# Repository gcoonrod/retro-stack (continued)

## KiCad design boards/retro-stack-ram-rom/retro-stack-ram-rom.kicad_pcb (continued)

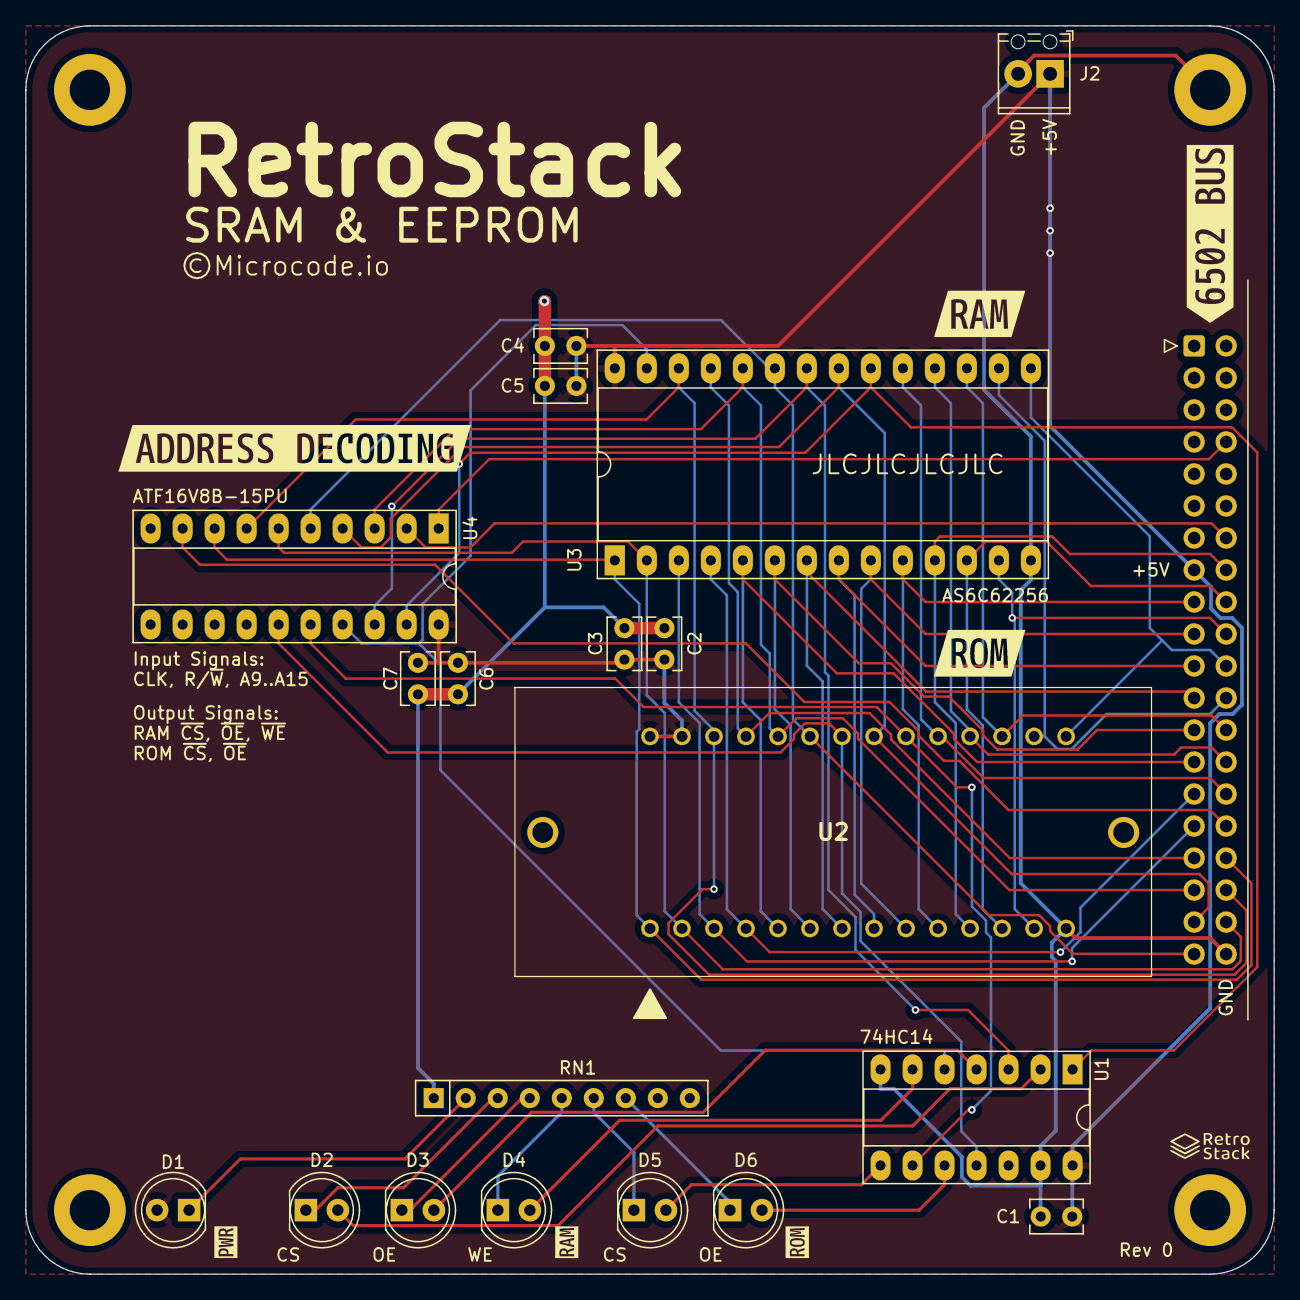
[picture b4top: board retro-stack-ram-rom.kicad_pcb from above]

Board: 2 copper layers, 99.1 x 99.1 mm, 31 parts (0 on the bottom side), 44 nets.

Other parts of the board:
kibuzzard-642C367F: G***; kibuzzard-642C367F
kibuzzard-642DBD4D: G***; kibuzzard-642DBD4D
kibuzzard-642DBD42: G***; kibuzzard-642DBD42
kibuzzard-642DC482: G***; kibuzzard-642DC482
kibuzzard-642888DE: G***; kibuzzard-642888DE
kibuzzard-6448402D: G***; kibuzzard-6448402D
kibuzzard-64484043: G***; kibuzzard-64484043

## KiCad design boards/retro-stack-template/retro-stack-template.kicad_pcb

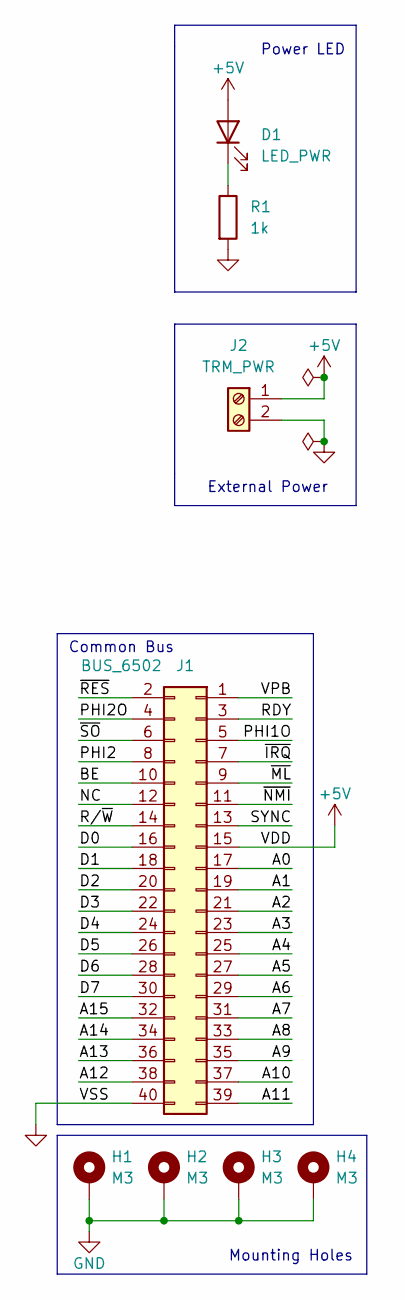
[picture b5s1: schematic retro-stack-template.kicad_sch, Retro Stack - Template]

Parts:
D1: LED_PWR; LED_D5.0mm
H1, H2, H3, H4: M3; MountingHole_3.2mm_M3_ISO7380_Pad
J1: BUS_6502; IDC-Header_2x20_P2.54mm_Horizontal
J2: TRM_PWR; TerminalBlock_Phoenix_MPT-0,5-2-2.54_1x02_P2.54mm_Horizontal; Mfr Part 1725656
R1: 1k; R_Axial_DIN0204_L3.6mm_D1.6mm_P5.08mm_Horizontal

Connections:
+5V: D1.2 (A), J1.15, J2.1
/A0: J1.17
/A1: J1.19
/A2: J1.21
/A3: J1.23
/A4: J1.25
/A5: J1.27
/A6: J1.29
/A7: J1.31
/A8: J1.33
/A9: J1.35
/A10: J1.37
/A11: J1.39
/A12: J1.38
/A13: J1.36
/A14: J1.34
/A15: J1.32
/BE: J1.10
/D0: J1.16
/D1: J1.18
/D2: J1.20
/D3: J1.22
/D4: J1.24
/D5: J1.26
/D6: J1.28
/D7: J1.30
/NC: J1.12
/PHI1O: J1.5
/PHI2: J1.8
/PHI2O: J1.4
/RDY: J1.3
/R/~W: J1.14
/SYNC: J1.13
/VPB: J1.1
/~IRQ: J1.7
/~ML: J1.9
/~NMI: J1.11
/~RES: J1.2
/~SO: J1.6
GND: H1.1, H2.1, H3.1, H4.1, J1.40, J2.2, R1.2
unnamed: D1.1 (K), R1.1

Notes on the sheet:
External Power
Common Bus
Power LED
Mounting Holes

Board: 2 copper layers, 11 parts (0 on the bottom side), 3 nets, no tracks yet.

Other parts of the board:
kibuzzard-642C36EF: G***; kibuzzard-642C36EF
kibuzzard-642C367F: G***; kibuzzard-642C367F
kibuzzard-642888DE: G***; kibuzzard-642888DE

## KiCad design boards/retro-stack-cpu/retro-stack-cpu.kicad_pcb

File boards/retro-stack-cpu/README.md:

# RetroStack - W65C02S CPU & High Speed Clock Module

This module contains the W65C02S CPU, a selectable high speed oscillator, and a selectable DS1813 reset signal manager.

## Schematic

Current schematic [pdf](./assets/schematic.pdf).

## PCB Layout & Render

## Known Issues

N/A

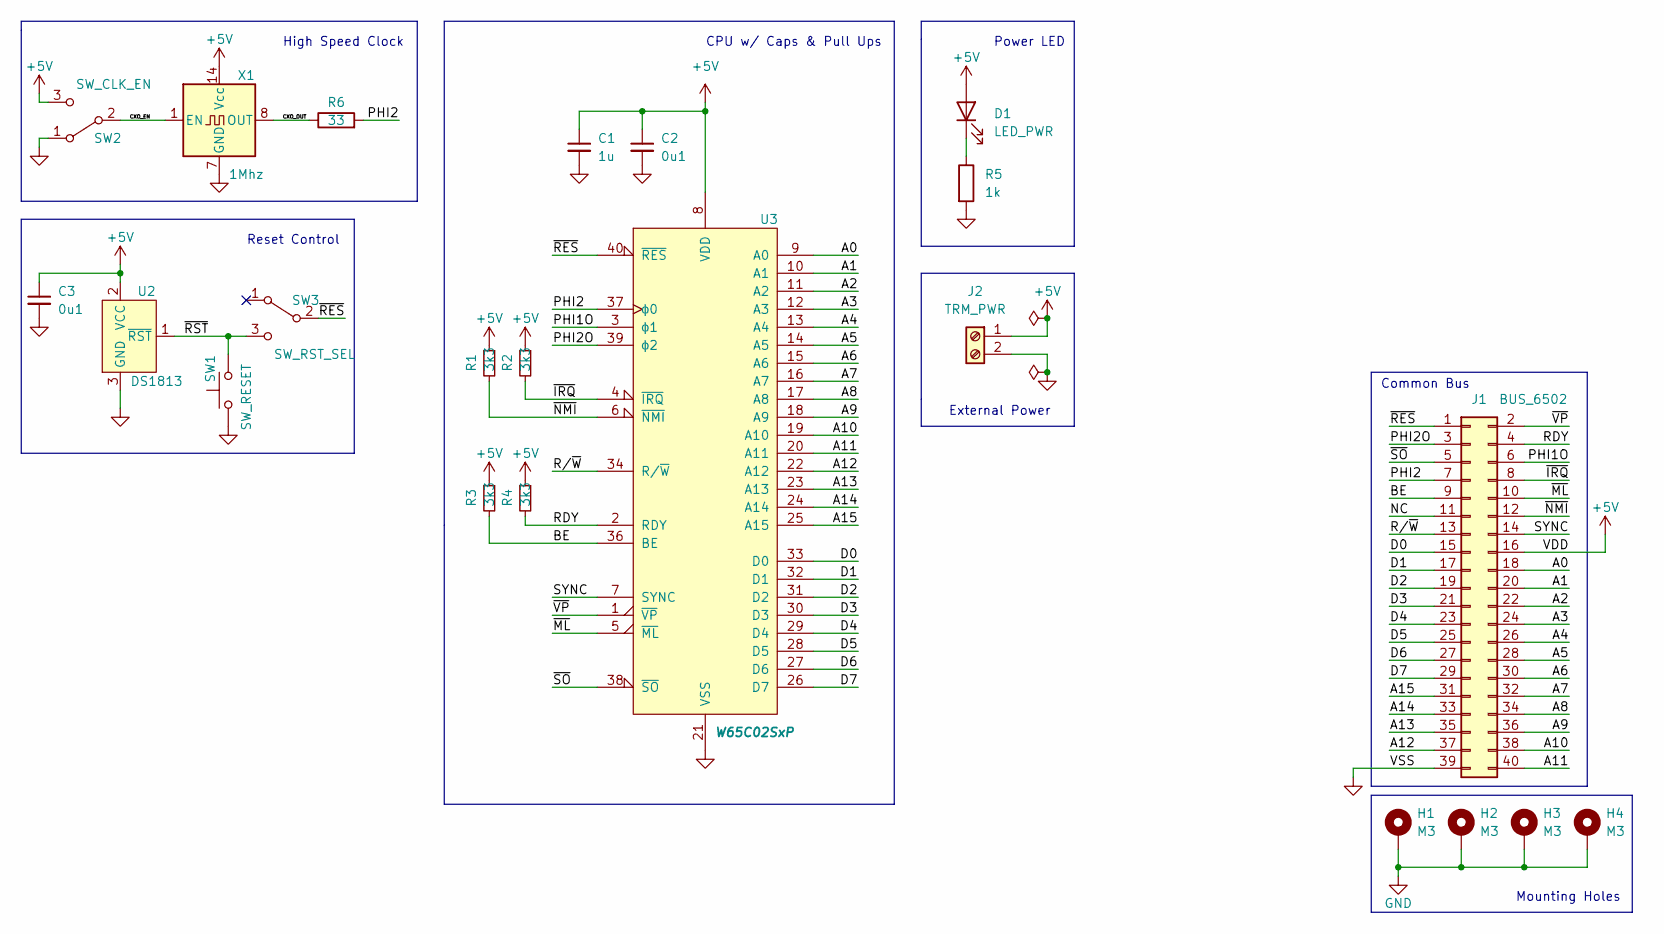
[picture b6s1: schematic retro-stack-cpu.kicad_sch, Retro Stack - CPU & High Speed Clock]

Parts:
C1: 1u; C_Rect_L4.0mm_W2.5mm_P2.50mm; Mfr Part FA18X7R1E105KRU06
C2, C3: 0u1; C_Rect_L4.0mm_W2.5mm_P2.50mm; Mfr Part RCER71E104K0A2H03B
D1: LED_PWR; LED_D5.0mm
H1, H2, H3, H4: M3; MountingHole_3.2mm_M3_ISO7380_Pad
J1: BUS_6502; PinSocket_2x20_P2.54mm_Vertical; Mfr Part 1979
J2: TRM_PWR; TerminalBlock_Phoenix_MPT-0,5-2-2.54_1x02_P2.54mm_Horizontal; Mfr Part 1725656
R1, R2, R3, R4: 3k3; R_Axial_DIN0204_L3.6mm_D1.6mm_P5.08mm_Horizontal; Mfr Part MBA02040C3301FRP00
R5: 1k; R_Axial_DIN0204_L3.6mm_D1.6mm_P5.08mm_Horizontal; Mfr Part MBA02040C1001FCT00
R6: 33; R_Axial_DIN0204_L3.6mm_D1.6mm_P5.08mm_Horizontal; Mfr Part MBA02040C3309FC100
SW1: SW_RESET; SW_Tactile_SPST_Angled_PTS645Vx58-2LFS; Mfr Part TS11-674-73-BK-100-RA-D
SW2: SW_CLK_EN; LC1258EENP1RLGR; Mfr Part LC1258EENP1RLGR
SW3: SW_RST_SEL; LC1258EENP1RLGR; Mfr Part LC1258EENP1RLGR
U2: DS1813; TO-92; Mfr Part DS1813-10+T&R
U3: W65C02SxP; DIP-40_W15.24mm_Socket_LongPads; Mfr Part W65C02S6TPG-14
X1: 1Mhz; Oscillator_DIP-14; Mfr Part MXO45T-2C-1M0000

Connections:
+5V: C1.1, C2.1, C3.1, D1.2 (A), J1.16, J2.1, R1.1, R2.1, R3.1, R4.1, SW2.3 (C), U2.2 (VCC), U3.8 (VDD), X1.14 (Vcc)
/A0: J1.18, U3.9 (A0)
/A1: J1.20, U3.10 (A1)
/A2: J1.22, U3.11 (A2)
/A3: J1.24, U3.12 (A3)
/A4: J1.26, U3.13 (A4)
/A5: J1.28, U3.14 (A5)
/A6: J1.30, U3.15 (A6)
/A7: J1.32, U3.16 (A7)
/A8: J1.34, U3.17 (A8)
/A9: J1.36, U3.18 (A9)
/A10: J1.38, U3.19 (A10)
/A11: J1.40, U3.20 (A11)
/A12: J1.37, U3.22 (A12)
/A13: J1.35, U3.23 (A13)
/A14: J1.33, U3.24 (A14)
/A15: J1.31, U3.25 (A15)
/BE: J1.9, R3.2, U3.36 (BE)
/CXO_EN: SW2.2 (B), X1.1 (EN)
/CXO_OUT: R6.1, X1.8 (OUT)
/D0: J1.15, U3.33 (D0)
/D1: J1.17, U3.32 (D1)
/D2: J1.19, U3.31 (D2)
/D3: J1.21, U3.30 (D3)
/D4: J1.23, U3.29 (D4)
/D5: J1.25, U3.28 (D5)
/D6: J1.27, U3.27 (D6)
/D7: J1.29, U3.26 (D7)
/NC: J1.11
/PHI1O: J1.6, U3.3 (ϕ1)
/PHI2: J1.7, R6.2, U3.37 (ϕ0)
/PHI2O: J1.3, U3.39 (ϕ2)
/RDY: J1.4, R4.2, U3.2 (RDY)
/R/~W: J1.13, U3.34 (R/~W)
/SYNC: J1.14, U3.7 (SYNC)
/~IRQ: J1.8, R2.2, U3.4 (~IRQ)
/~ML: J1.10, U3.5 (~ML)
/~NMI: J1.12, R1.2, U3.6 (~NMI)
/~RES: J1.1, SW3.2 (B), U3.40 (~RES)
/~RST: SW1.2, SW3.3 (C), U2.1 (~RST)
/~SO: J1.5, U3.38 (~SO)
/~VP: J1.2, U3.1 (~VP)
GND: C1.2, C2.2, C3.2, H1.1, H2.1, H3.1, H4.1, J1.39, J2.2, R5.2, SW1.1, SW2.1 (A), U2.3 (GND), U3.21 (VSS), X1.7 (GND)
unnamed: D1.1 (K), R5.1

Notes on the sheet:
CPU w/ Caps & Pull Ups
Common Bus
Power LED
High Speed Clock
External Power
Reset Control
Mounting Holes

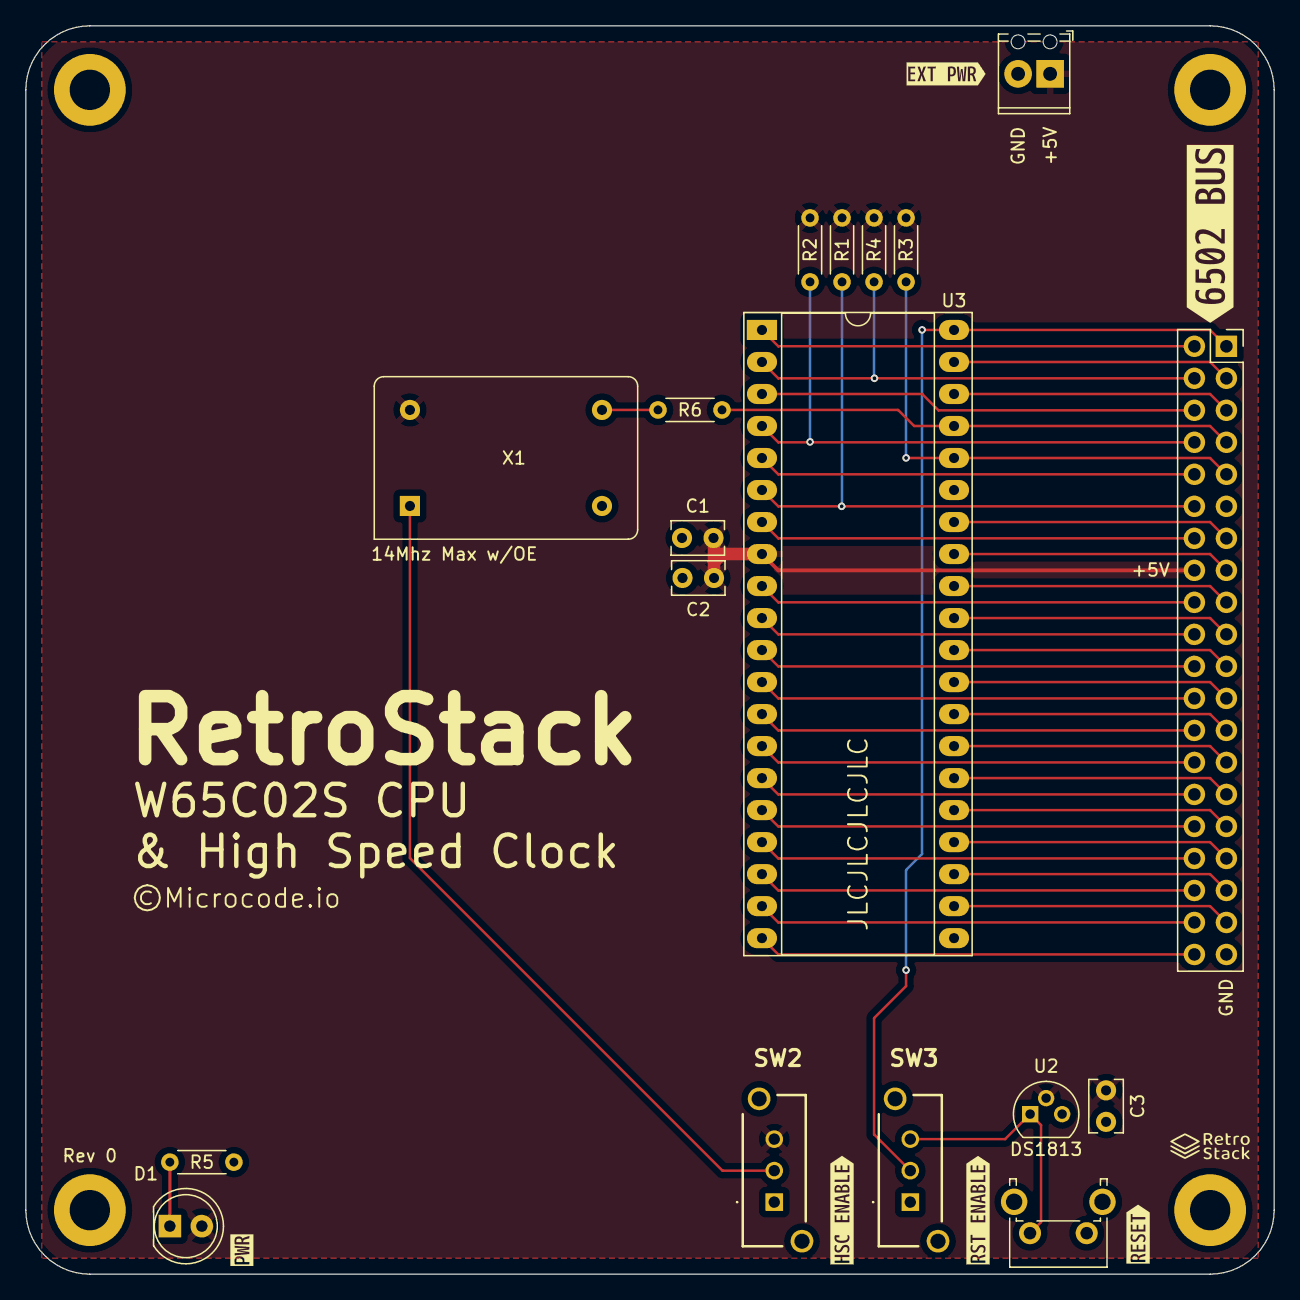
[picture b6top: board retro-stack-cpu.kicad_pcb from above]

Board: 2 copper layers, 99.1 x 99.1 mm, 28 parts (0 on the bottom side), 43 nets.

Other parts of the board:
kibuzzard-642C33B0: G***; kibuzzard-642C33B0
kibuzzard-642C36EF: G***; kibuzzard-642C36EF
kibuzzard-642C367F: G***; kibuzzard-642C367F
kibuzzard-642C3375: G***; kibuzzard-642C3375
kibuzzard-642C3403: G***; kibuzzard-642C3403
kibuzzard-642888DE: G***; kibuzzard-642888DE

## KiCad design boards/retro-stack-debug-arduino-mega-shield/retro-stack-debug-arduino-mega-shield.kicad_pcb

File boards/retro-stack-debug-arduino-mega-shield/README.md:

# RetroStack - Arduino Mega Debug Shield

This Arduino Mega shield is designed to easily connect to the RetroStack Debug board via a 40 pin IDC connector.

## Schematic

Current schematic [pdf](./assets/schematic.pdf).

## PCB Layout & Render

## Known Issues

- 6502 Bus is backwards. Pin 1 should be RESB but is VPB instead.
- PHI2 should be connected to one of the digital pins that support interrupts (2, 3, etc)
  - Consider adding jumpers to send a few signals to interrupt pins.
- Power seems to be leaking between the arduino and the RetroStack. Needs diodes?

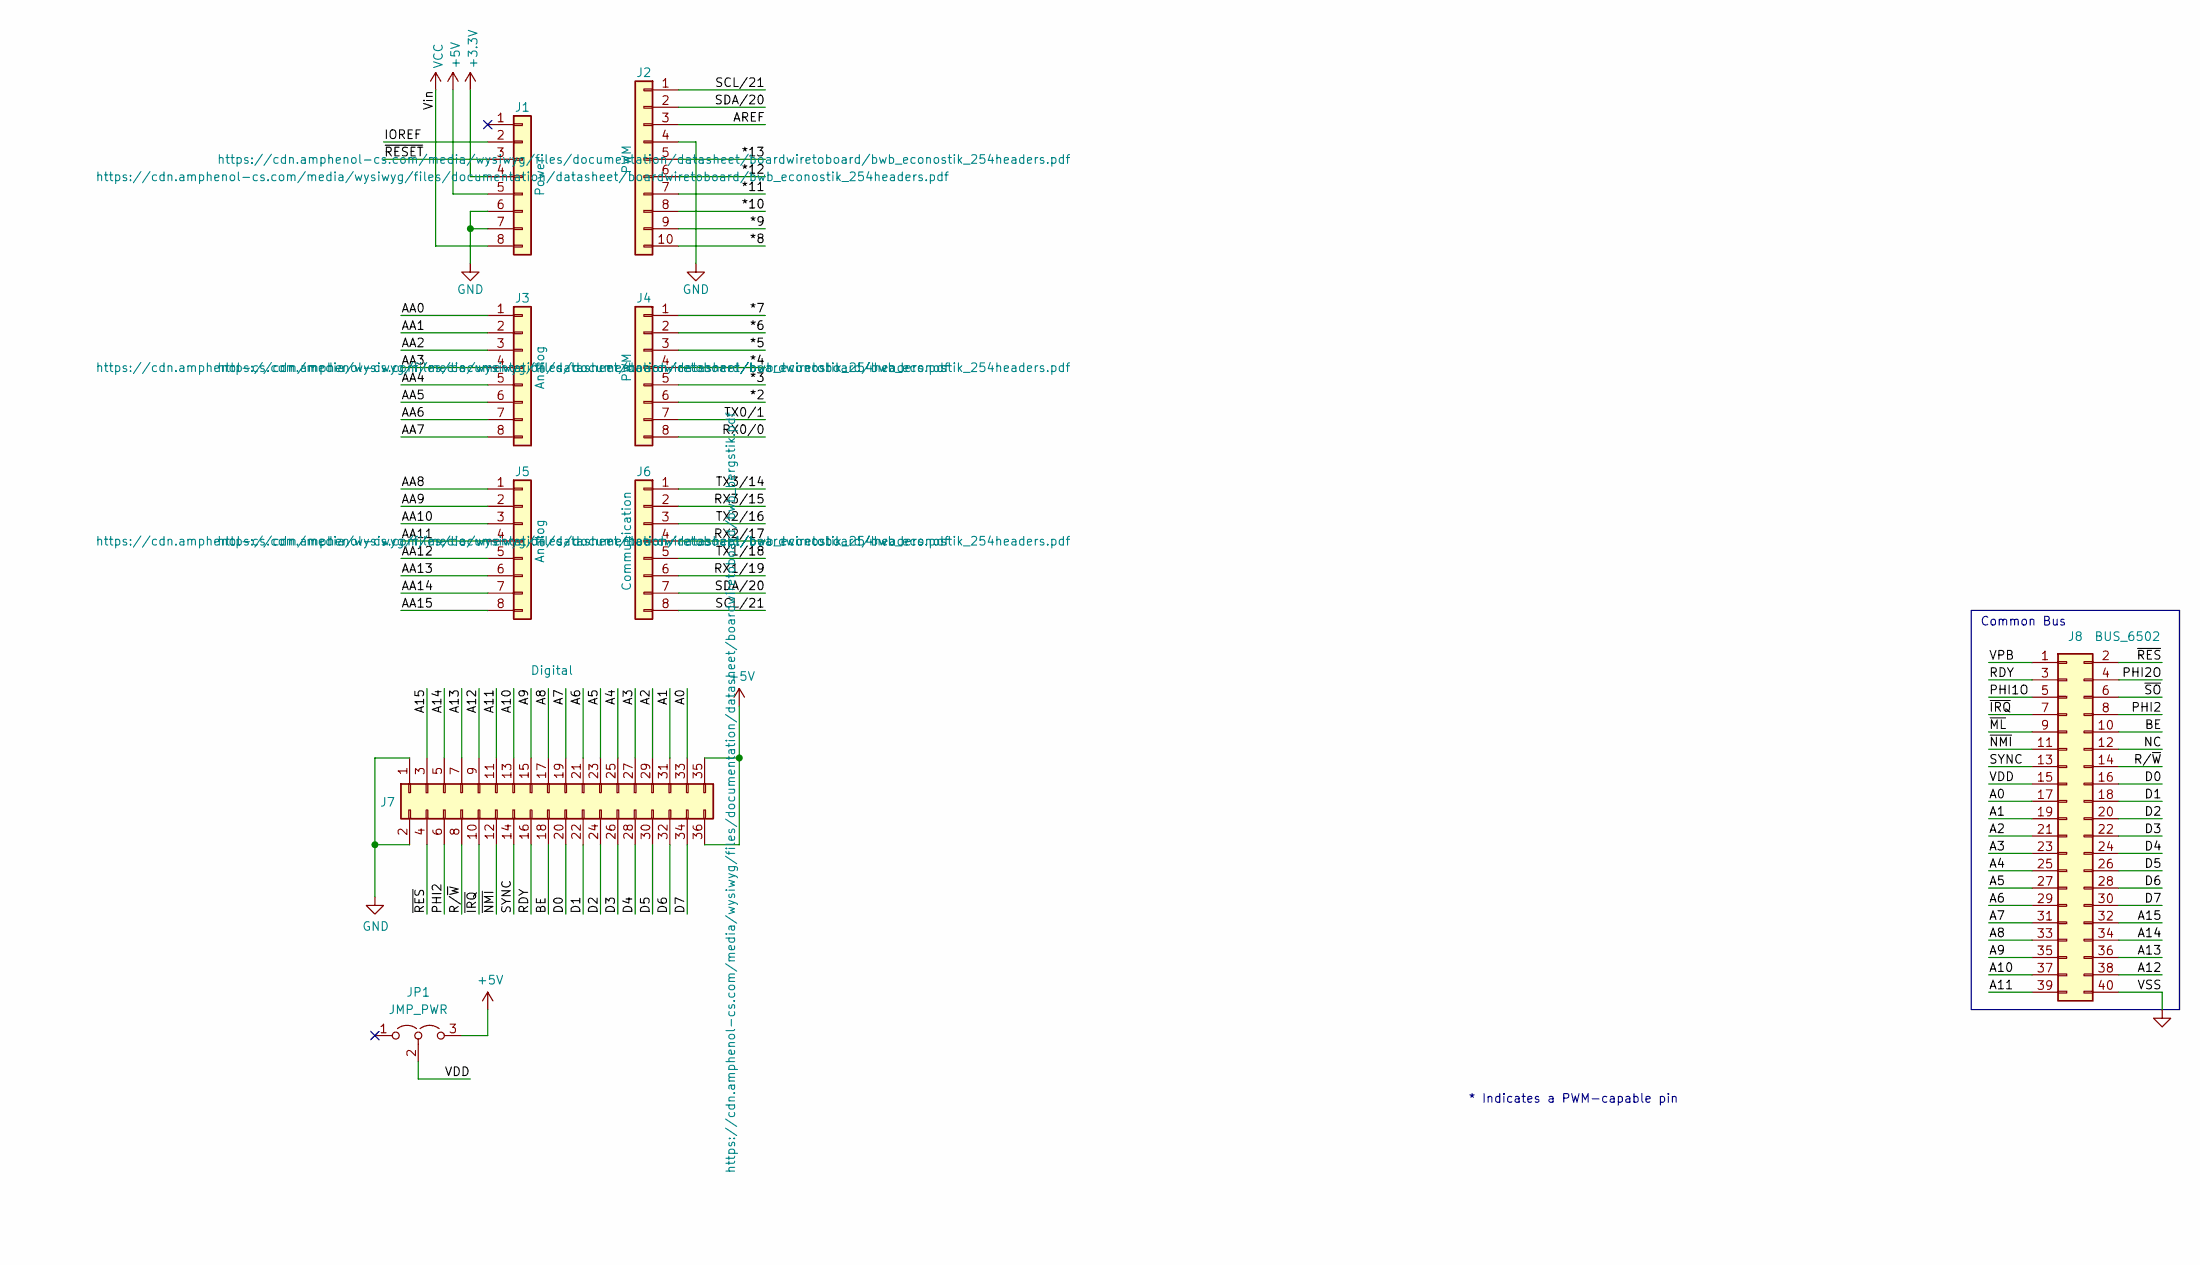
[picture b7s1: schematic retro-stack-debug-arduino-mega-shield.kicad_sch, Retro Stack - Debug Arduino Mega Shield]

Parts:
J1: Power; PinSocket_1x08_P2.54mm_Vertical; Mfr Part 10129378-908001BLF
J2: PWM; PinSocket_1x10_P2.54mm_Vertical; Mfr Part 10129378-910001BLF
J3, J5: Analog; PinSocket_1x08_P2.54mm_Vertical; Mfr Part 10129378-908001BLF
J4: PWM; PinSocket_1x08_P2.54mm_Vertical; Mfr Part 10129378-908001BLF
J6: Communication; PinSocket_1x08_P2.54mm_Vertical; Mfr Part 10129378-908001BLF
J7: Digital; PinSocket_2x18_P2.54mm_Vertical; Mfr Part 77313-818-36LF
J8: BUS_6502; IDC-Header_2x20_P2.54mm_Vertical; Mfr Part 30340-6002HB
JP1: JMP_PWR; PinHeader_1x03_P2.54mm_Vertical; Mfr Part 10129378-903001BLF

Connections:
+3V3: J1.4
+5V: J1.5, J7.35, J7.36, JP1.3 (B)
/*2: J4.6
/*3: J4.5
/*4: J4.4
/*5: J4.3
/*6: J4.2
/*7: J4.1
/*8: J2.10
/*9: J2.9
/*10: J2.8
/*11: J2.7
/*12: J2.6
/*13: J2.5
/A0: J7.33, J8.17
/A1: J7.31, J8.19
/A2: J7.29, J8.21
/A3: J7.27, J8.23
/A4: J7.25, J8.25
/A5: J7.23, J8.27
/A6: J7.21, J8.29
/A7: J7.19, J8.31
/A8: J7.17, J8.33
/A9: J7.15, J8.35
/A10: J7.13, J8.37
/A11: J7.11, J8.39
/A12: J7.9, J8.38
/A13: J7.7, J8.36
/A14: J7.5, J8.34
/A15: J7.3, J8.32
/AA0: J3.1
/AA1: J3.2
/AA2: J3.3
/AA3: J3.4
/AA4: J3.5
/AA5: J3.6
/AA6: J3.7
/AA7: J3.8
/AA8: J5.1
/AA9: J5.2
/AA10: J5.3
/AA11: J5.4
/AA12: J5.5
/AA13: J5.6
/AA14: J5.7
/AA15: J5.8
/AREF: J2.3
/BE: J7.18, J8.10
/D0: J7.20, J8.16
/D1: J7.22, J8.18
/D2: J7.24, J8.20
/D3: J7.26, J8.22
/D4: J7.28, J8.24
/D5: J7.30, J8.26
/D6: J7.32, J8.28
/D7: J7.34, J8.30
/IOREF: J1.2
/NC: J8.12
/PHI1O: J8.5
/PHI2: J7.6, J8.8
/PHI2O: J8.4
/RDY: J7.16, J8.3
/RX0/0: J4.8
/RX1/19: J6.6
/RX2/17: J6.4
/RX3/15: J6.2
/R/~W: J7.8, J8.14
/SCL/21: J2.1, J6.8
/SDA/20: J2.2, J6.7
/SYNC: J7.14, J8.13
/TX0/1: J4.7
/TX1/18: J6.5
/TX2/16: J6.3
/TX3/14: J6.1
/VDD: J8.15, JP1.2 (C)
/VPB: J8.1
/~IRQ: J7.10, J8.7
/~ML: J8.9
/~NMI: J7.12, J8.11
/~RESET: J1.3
/~RES: J7.4, J8.2
/~SO: J8.6
GND: J1.6, J1.7, J2.4, J7.1, J7.2, J8.40
VCC: J1.8

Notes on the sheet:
* Indicates a PWM-capable pin
Common Bus

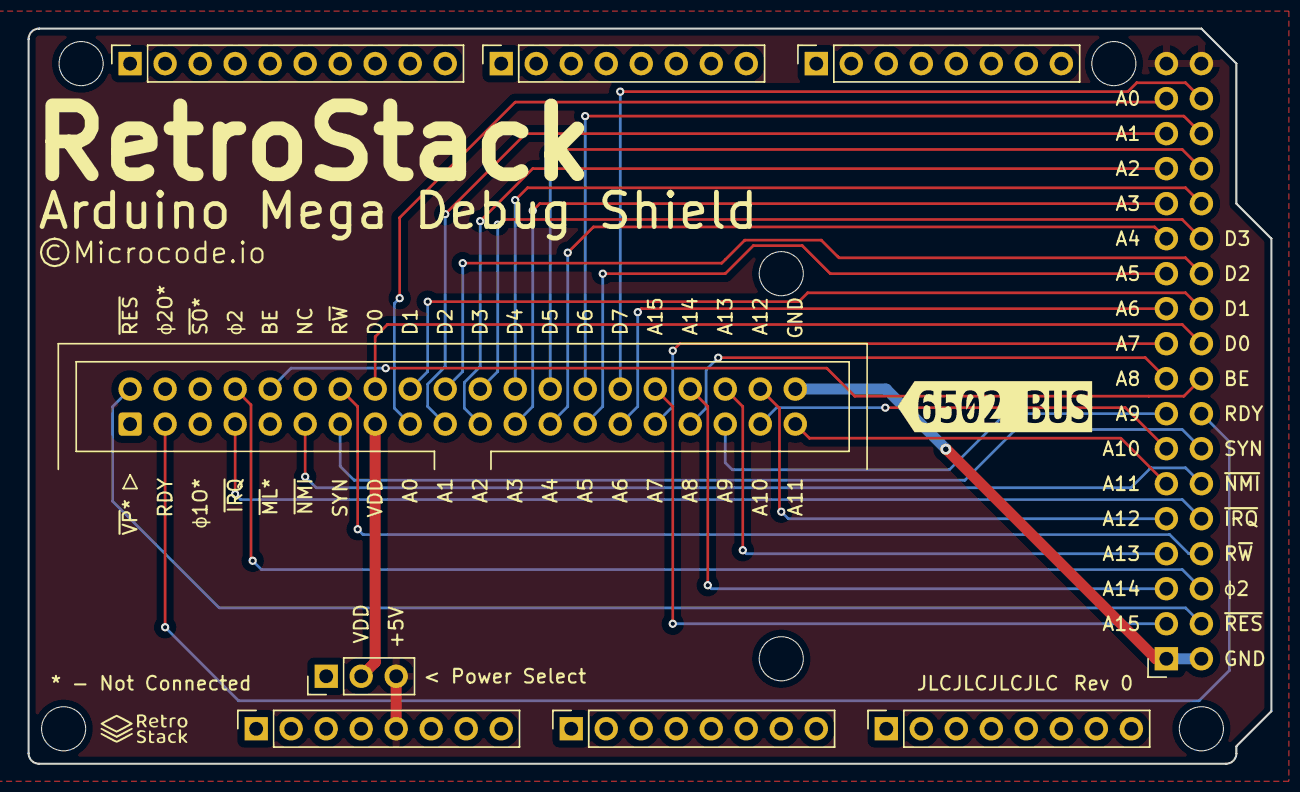
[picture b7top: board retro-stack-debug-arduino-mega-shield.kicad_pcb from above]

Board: 2 copper layers, 90.2 x 53.3 mm, 16 parts (0 on the bottom side), 37 nets.

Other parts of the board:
MH1, MH2, MH3, MH4, MH5, MH6: MountingHole_3.2mm
kibuzzard-642888DE: G***; kibuzzard-642888DE

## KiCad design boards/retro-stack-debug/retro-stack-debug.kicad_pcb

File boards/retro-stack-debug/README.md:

# RetroStack - Debug Interface & Signal Monitor Module

This module provides a 40 pin IDC connection for use with an external debugging tool/circuit. In addition, all of the Address and Data signals and most of the control signals are routed through buffers to drive LEDs. The buffers can be disabled by the Display switch in the upper left when operating at higher speeds.

## Schematic

Current schematic [pdf](./assets/schematic.pdf).

## PCB Layout & Render

## Known Issues

N/A

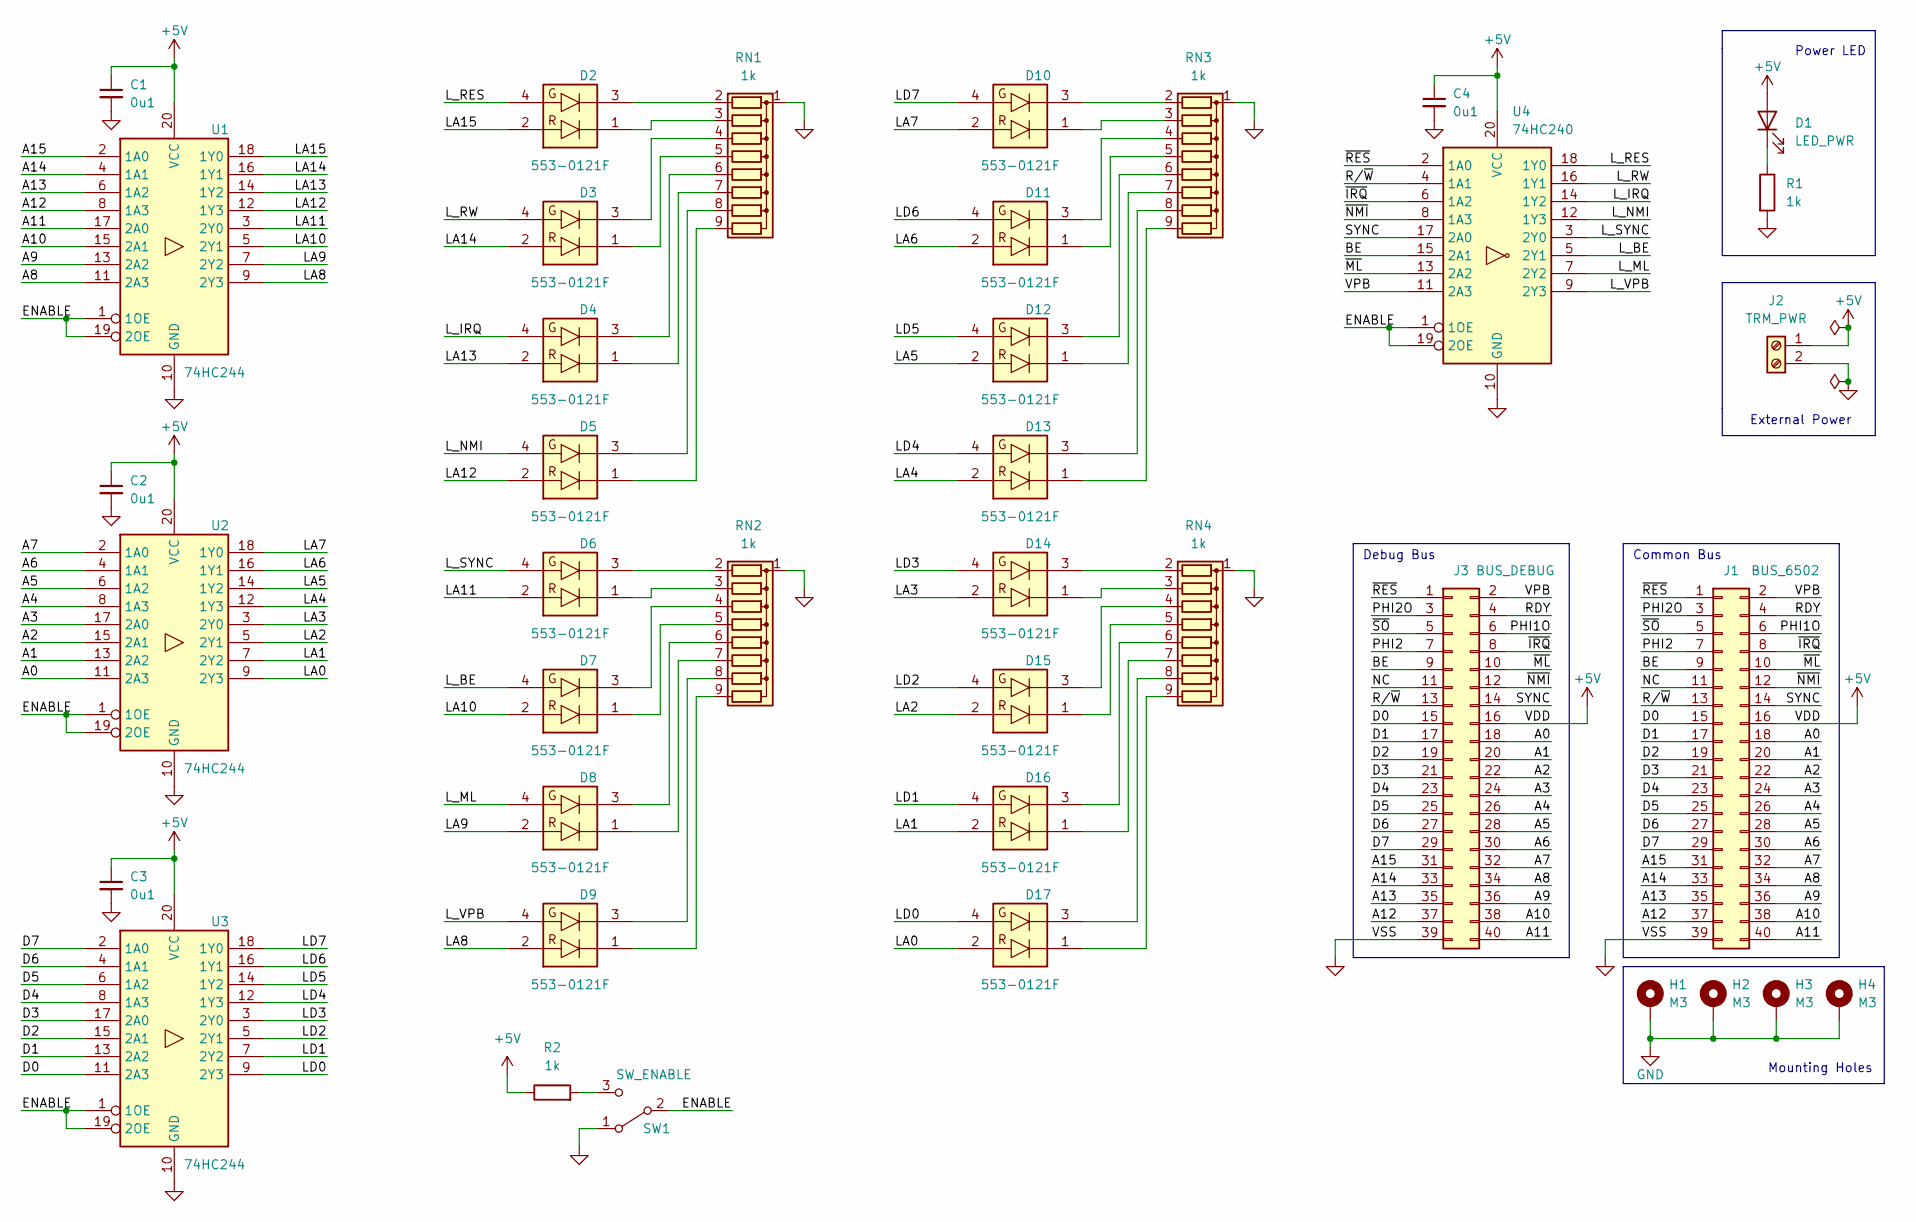
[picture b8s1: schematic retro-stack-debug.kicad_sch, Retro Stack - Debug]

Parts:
C1, C2, C3, C4: 0u1; C_Disc_D3.0mm_W2.0mm_P2.50mm; Mfr Part K104K15X7RF5TL2
D1: LED_PWR; LED_D5.0mm
D2, D3, D4, D5, D6, D7, D8, D9, D10, D11, D12, D13, D14, D15, D16, D17: 553-0121F; 5530121F; Mfr Part 553-0121F
H1, H2, H3, H4: M3; MountingHole_3.2mm_M3_ISO7380_Pad
J1: BUS_6502; PinSocket_2x20_P2.54mm_Vertical
J2: TRM_PWR; TerminalBlock_Phoenix_MPT-0,5-2-2.54_1x02_P2.54mm_Horizontal; Mfr Part 1725656
J3: BUS_DEBUG; IDC-Header_2x20_P2.54mm_Vertical; Mfr Part 30340-6002HB
R1, R2: 1k; R_Axial_DIN0204_L3.6mm_D1.6mm_P5.08mm_Horizontal; Mfr Part MBA02040C1001FCT00
RN1, RN2, RN3, RN4: 1k; R_Array_SIP9; Mfr Part 4609X-101-102LF
SW1: SW_ENABLE; LC1258EENP1RLGR; Mfr Part LC1258EENP1RLGR
U1, U2, U3: 74HC244; DIP-20_W7.62mm_LongPads; Mfr Part SN74HC244N
U4: 74HC240; DIP-20_W7.62mm_LongPads; Mfr Part SN74HC240N

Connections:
+5V: C1.1, C2.1, C3.1, C4.1, D1.2 (A), J1.16, J2.1, J3.16, R2.1, U1.20 (VCC), U2.20 (VCC), U3.20 (VCC), U4.20 (VCC)
/A0: J1.18, J3.18, U2.11 (2A3)
/A1: J1.20, J3.20, U2.13 (2A2)
/A2: J1.22, J3.22, U2.15 (2A1)
/A3: J1.24, J3.24, U2.17 (2A0)
/A4: J1.26, J3.26, U2.8 (1A3)
/A5: J1.28, J3.28, U2.6 (1A2)
/A6: J1.30, J3.30, U2.4 (1A1)
/A7: J1.32, J3.32, U2.2 (1A0)
/A8: J1.34, J3.34, U1.11 (2A3)
/A9: J1.36, J3.36, U1.13 (2A2)
/A10: J1.38, J3.38, U1.15 (2A1)
/A11: J1.40, J3.40, U1.17 (2A0)
/A12: J1.37, J3.37, U1.8 (1A3)
/A13: J1.35, J3.35, U1.6 (1A2)
/A14: J1.33, J3.33, U1.4 (1A1)
/A15: J1.31, J3.31, U1.2 (1A0)
/BE: J1.9, J3.9, U4.15 (2A1)
/D0: J1.15, J3.15, U3.11 (2A3)
/D1: J1.17, J3.17, U3.13 (2A2)
/D2: J1.19, J3.19, U3.15 (2A1)
/D3: J1.21, J3.21, U3.17 (2A0)
/D4: J1.23, J3.23, U3.8 (1A3)
/D5: J1.25, J3.25, U3.6 (1A2)
/D6: J1.27, J3.27, U3.4 (1A1)
/D7: J1.29, J3.29, U3.2 (1A0)
/ENABLE: SW1.2 (B), U1.1 (1OE), U1.19 (2OE), U2.1 (1OE), U2.19 (2OE), U3.1 (1OE), U3.19 (2OE), U4.1 (1OE), U4.19 (2OE)
/LA0: D17.2, U2.9 (2Y3)
/LA1: D16.2, U2.7 (2Y2)
/LA2: D15.2, U2.5 (2Y1)
/LA3: D14.2, U2.3 (2Y0)
/LA4: D13.2, U2.12 (1Y3)
/LA5: D12.2, U2.14 (1Y2)
/LA6: D11.2, U2.16 (1Y1)
/LA7: D10.2, U2.18 (1Y0)
/LA8: D9.2, U1.9 (2Y3)
/LA9: D8.2, U1.7 (2Y2)
/LA10: D7.2, U1.5 (2Y1)
/LA11: D6.2, U1.3 (2Y0)
/LA12: D5.2, U1.12 (1Y3)
/LA13: D4.2, U1.14 (1Y2)
/LA14: D3.2, U1.16 (1Y1)
/LA15: D2.2, U1.18 (1Y0)
/LD0: D17.4, U3.9 (2Y3)
/LD1: D16.4, U3.7 (2Y2)
/LD2: D15.4, U3.5 (2Y1)
/LD3: D14.4, U3.3 (2Y0)
/LD4: D13.4, U3.12 (1Y3)
/LD5: D12.4, U3.14 (1Y2)
/LD6: D11.4, U3.16 (1Y1)
/LD7: D10.4, U3.18 (1Y0)
/L_BE: D7.4, U4.5 (2Y1)
/L_IRQ: D4.4, U4.14 (1Y2)
/L_ML: D8.4, U4.7 (2Y2)
/L_NMI: D5.4, U4.12 (1Y3)
/L_RES: D2.4, U4.18 (1Y0)
/L_RW: D3.4, U4.16 (1Y1)
/L_SYNC: D6.4, U4.3 (2Y0)
/L_VPB: D9.4, U4.9 (2Y3)
/NC: J1.11, J3.11
/PHI1O: J1.6, J3.6
/PHI2: J1.7, J3.7
/PHI2O: J1.3, J3.3
/RDY: J1.4, J3.4
/R/~W: J1.13, J3.13, U4.4 (1A1)
/SYNC: J1.14, J3.14, U4.17 (2A0)
/VPB: J1.2, J3.2, U4.11 (2A3)
/~IRQ: J1.8, J3.8, U4.6 (1A2)
/~ML: J1.10, J3.10, U4.13 (2A2)
/~NMI: J1.12, J3.12, U4.8 (1A3)
/~RES: J1.1, J3.1, U4.2 (1A0)
/~SO: J1.5, J3.5
GND: C1.2, C2.2, C3.2, C4.2, H1.1, H2.1, H3.1, H4.1, J1.39, J2.2, J3.39, R1.2, RN1.1 (common), RN2.1 (common), RN3.1 (common), RN4.1 (common), SW1.1 (A), U1.10 (GND), U2.10 (GND), U3.10 (GND), U4.10 (GND)
unnamed: D1.1 (K), R1.1
unnamed: D2.1, RN1.3 (R2)
unnamed: D2.3, RN1.2 (R1)
unnamed: D3.1, RN1.5 (R4)
unnamed: D3.3, RN1.4 (R3)
unnamed: D4.1, RN1.7 (R6)
unnamed: D4.3, RN1.6 (R5)
unnamed: D5.1, RN1.9 (R8)
unnamed: D5.3, RN1.8 (R7)
unnamed: D6.1, RN2.3 (R2)
unnamed: D6.3, RN2.2 (R1)
unnamed: D7.1, RN2.5 (R4)
unnamed: D7.3, RN2.4 (R3)
unnamed: D8.1, RN2.7 (R6)
unnamed: D8.3, RN2.6 (R5)
unnamed: D9.1, RN2.9 (R8)
unnamed: D9.3, RN2.8 (R7)
unnamed: D10.1, RN3.3 (R2)
unnamed: D10.3, RN3.2 (R1)
unnamed: D11.1, RN3.5 (R4)
unnamed: D11.3, RN3.4 (R3)
unnamed: D12.1, RN3.7 (R6)
unnamed: D12.3, RN3.6 (R5)
unnamed: D13.1, RN3.9 (R8)
unnamed: D13.3, RN3.8 (R7)
unnamed: D14.1, RN4.3 (R2)
unnamed: D14.3, RN4.2 (R1)
unnamed: D15.1, RN4.5 (R4)
unnamed: D15.3, RN4.4 (R3)
unnamed: D16.1, RN4.7 (R6)
unnamed: D16.3, RN4.6 (R5)
unnamed: D17.1, RN4.9 (R8)
unnamed: D17.3, RN4.8 (R7)
unnamed: R2.2, SW1.3 (C)

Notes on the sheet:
Debug Bus
External Power
Common Bus
Power LED
Mounting Holes

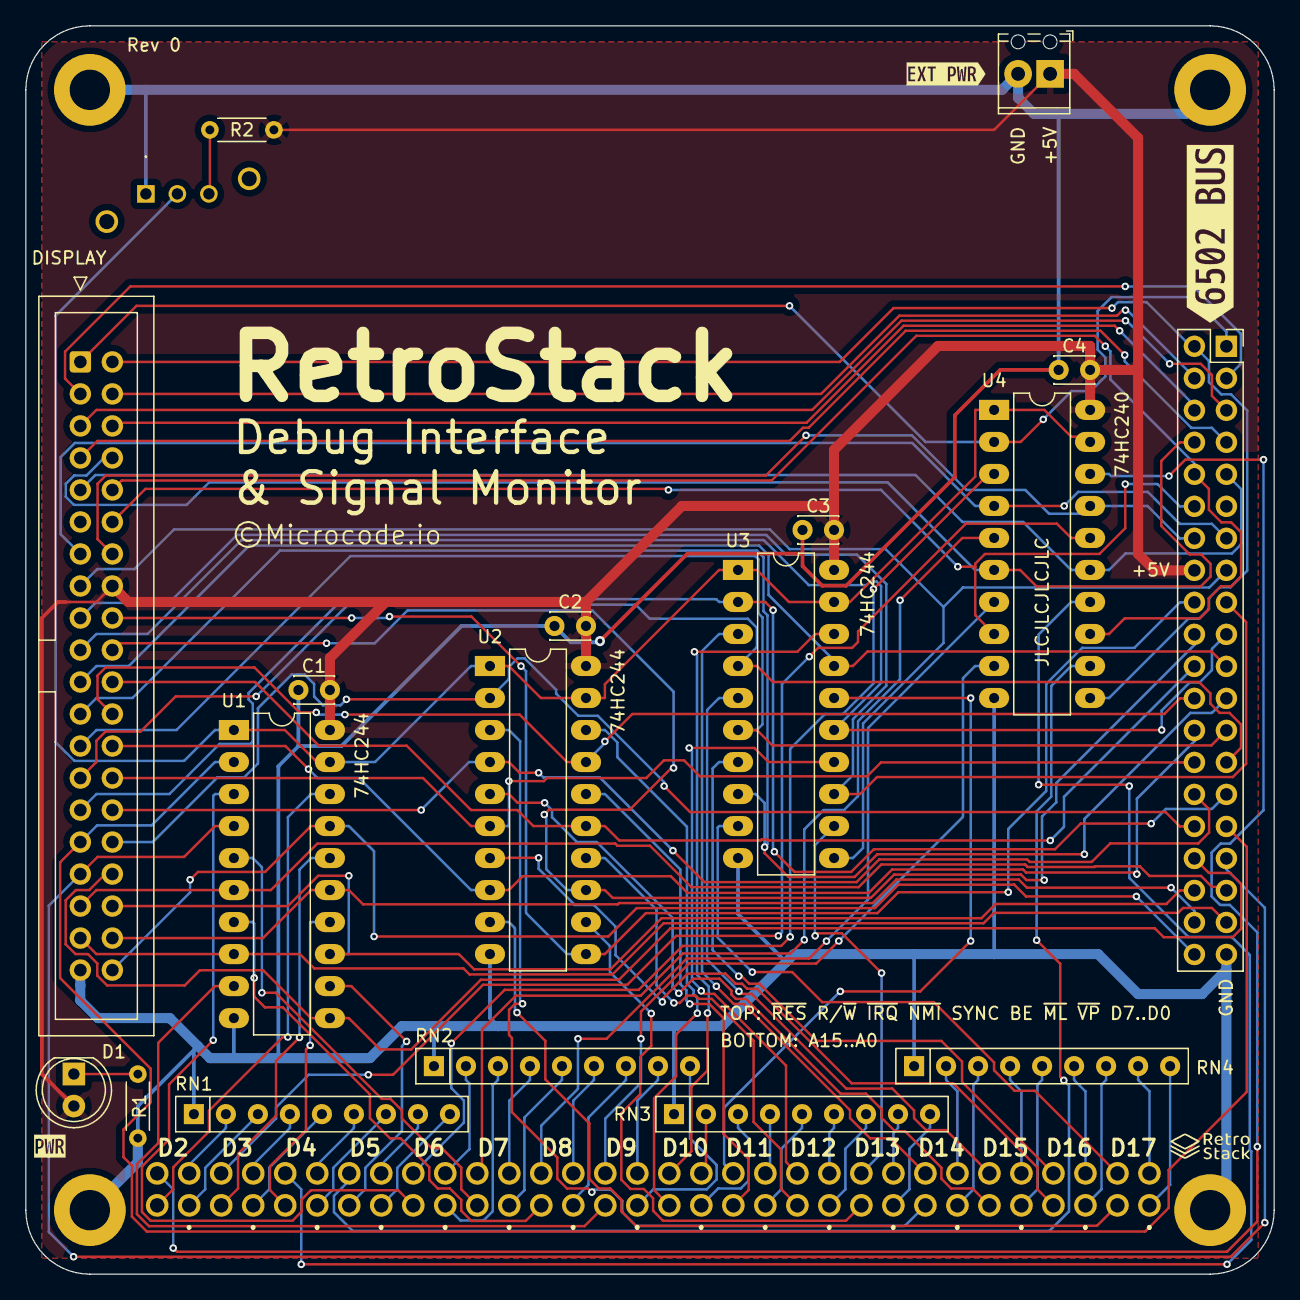
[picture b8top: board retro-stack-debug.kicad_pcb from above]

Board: 2 copper layers, 99.1 x 99.1 mm, 42 parts (0 on the bottom side), 107 nets.

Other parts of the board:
kibuzzard-642C36EF: G***; kibuzzard-642C36EF
kibuzzard-642C367F: G***; kibuzzard-642C367F
kibuzzard-642888DE: G***; kibuzzard-642888DE

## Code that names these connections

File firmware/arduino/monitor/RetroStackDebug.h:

// Copyright 2023 Greg Coonrod
// 
// Licensed under the Apache License, Version 2.0 (the "License");
// you may not use this file except in compliance with the License.
// You may obtain a copy of the License at
// 
//     http://www.apache.org/licenses/LICENSE-2.0
// 
// Unless required by applicable law or agreed to in writing, software
// distributed under the License is distributed on an "AS IS" BASIS,
// WITHOUT WARRANTIES OR CONDITIONS OF ANY KIND, either express or implied.
// See the License for the specific language governing permissions and
// limitations under the License.

#include <stdint.h>

#ifndef RETROSTACKDEBUG_H
#define RETROSTACKDEBUG_H

// Define the memory ranges
#define RAM_START 0x0000
#define RAM_END   0x3FFF
#define RAM_SIZE  (RAM_END - RAM_START + 1)
#define inRAM(address) (address >= RAM_START && address <= RAM_END)

#define ROM_START 0x8000
#define ROM_END   0xFFFF
#define ROM_SIZE  (ROM_END - ROM_START + 1)
#define inROM(address) (address >= ROM_START && address <= ROM_END)

// Define the address and data pins

// reverse the order of the address pins
//const char ADDR[] = {22, 24, 26, 28, 30, 32, 34, 36, 38, 40, 42, 44, 46, 48, 50, 52};
const char ADDR[] = {52, 50, 48, 46, 44, 42, 40, 38, 36, 34, 32, 30, 28, 26, 24, 22};

//const char DATA[] = {37, 35, 33, 31, 29, 27, 25, 23};
const char DATA[] = {23, 25, 27, 29, 31, 33, 35, 37};


// Define the control pins
#define BE      39
#define RDY     41
#define SYNC    43
#define NMIB    45
#define IRQB    47
#define RWB     49
#define PHI2    2
#define RESB    53

// Op Codes
#define NOP 0xEA

// Define functions
uint8_t readROM(uint16_t address);
uint8_t readRAM(uint16_t address);
uint16_t readAddress();
void setDataDirection(int direction);
void setAddressDirection(int direction);
void setControlDirections(uint8_t mask, uint8_t direction);
uint8_t readData();
void writeData(uint8_t data);


#endif

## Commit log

2023-04-01 Initial template setup.
2023-04-01 Initial board template design.
2023-04-02 Completed initial schematic and parts selection.
2023-04-03 Rev 0 of the power and clock card ordered.
2023-04-04 CPU board rev0 schematic and layout complete.
2023-04-05 Rev 0 schematic and pcb complete for RAM/ROM board.
2023-04-06 Update template
2023-04-07 Initial schematic and layout complete for VIA board.
2023-04-11 Initial design and layout of arduino debug shield.
2023-04-11 Minor updates.
2023-04-11 Update pwr and clk mod docs.
2023-04-11 Completed rev 0 of cpu, debug, and debug shield boards.
2023-04-11 Update documentation for recently completed board revisions.
2023-04-14 Update template to use right angle idc instead of vertical pin socket.
2023-04-19 Initial monitor program for the Debug module.
2023-04-22 Initial monitor program with basic ROM emulation.
2023-04-22 Readme updates
2023-04-24 Start work on a PLD test circuit.
2023-04-25 First working memory pld coded.
2023-04-25 Update ram/rom to only use pld.
2023-04-27 Initial PLD test and RAM/ROM board.
2023-05-03 Update documentation to include latest boards and firmware.
2023-05-10 New assembly programs and docs updates.
2023-05-15 LCD working in 8 bit mode.
2023-06-14 add latest set of kicad parts
2023-06-14 Minor board updates and nano-acia
2023-06-14 Readme
2023-07-12 Rev 0 of min sbc complete. Many issues. Start new Rev.
